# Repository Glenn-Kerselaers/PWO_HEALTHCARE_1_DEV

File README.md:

PWO_HEALTHCARE_1_DEV
====================

Project from PXL for Glenn Kerselaers and Devlin Voets. IMU modules with Bluetooth (BLE) interface for communication with PC.

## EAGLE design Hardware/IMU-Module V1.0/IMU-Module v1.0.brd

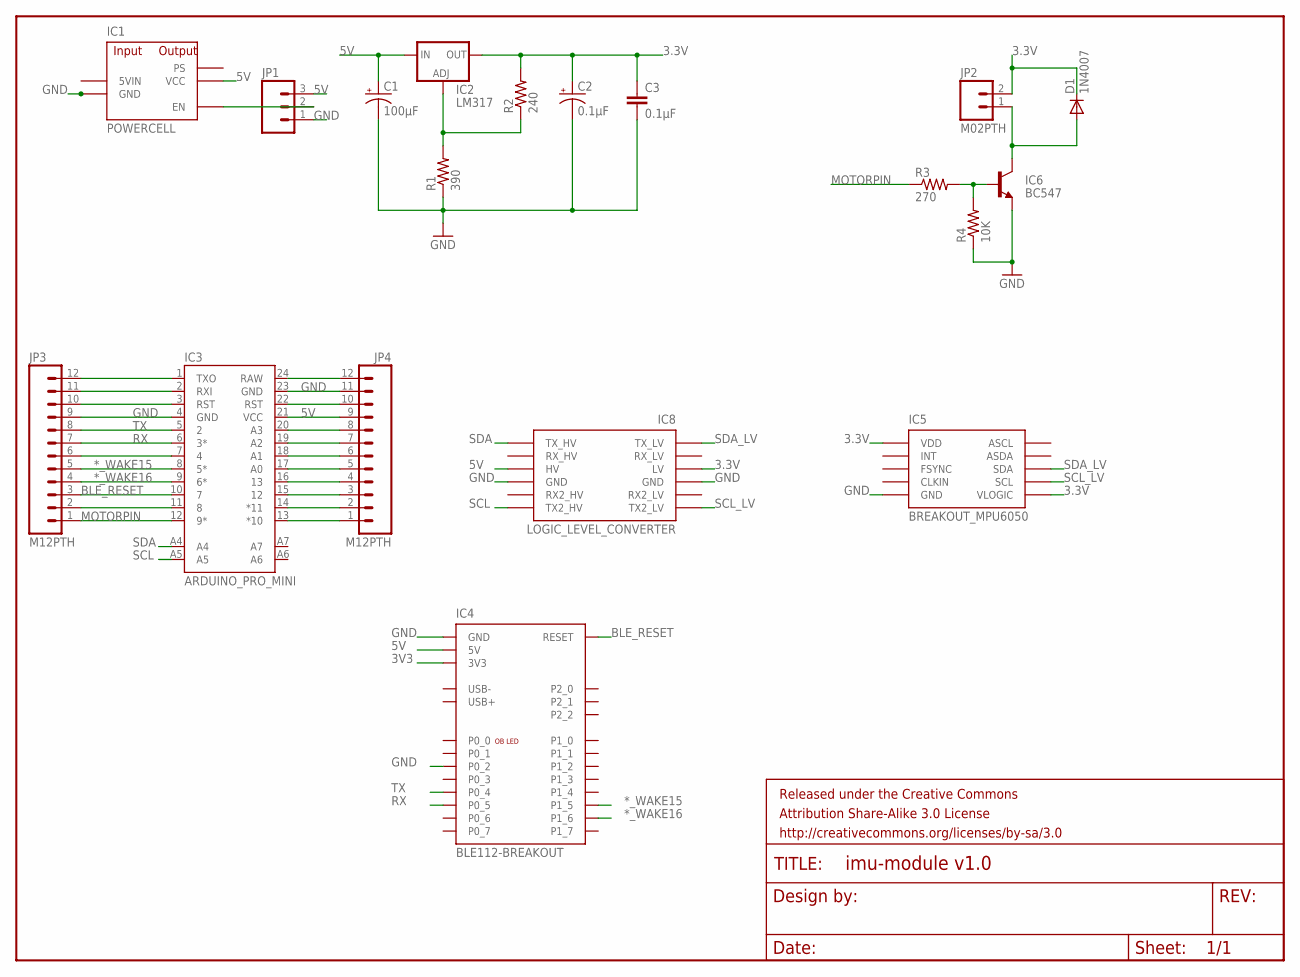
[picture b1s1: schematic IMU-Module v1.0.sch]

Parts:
C1: 100µF; CPOL-RADIAL-100UF-25V
C2: 0.1µF; CPOL-RADIAL-10UF-25V
C3: 0.1µF; 1206
D1: 1N4007; DIODE-1N4001-KIT
FRAME1: FRAME-LETTER; CREATIVE_COMMONS
IC1: POWERCELL
IC2: LM317; SOT223
IC3: ARDUINO_PRO_MINI
IC4: BLE112-BREAKOUT
IC5: BREAKOUT_MPU6050
IC6: BC547; TO-92
IC8: LOGIC_LEVEL_CONVERTER
JP1: M03PTH; 1X03
JP2: M02PTH; 1X02
JP3, JP4: M12PTH; 1X12
R1: 390; 1206
R2: 240; 1206
R3: 270; 1206
R4: 10K; 1206

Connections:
3.3V: C2.1 (+), C3.1, D1.C, IC2.2 (OUT), IC5.VDD, IC5.VLOGIC, IC8.LV, JP2.2, R2.2
3V3: IC4.3V3
5V: C1.1 (+), IC1.VCC, IC2.3 (IN), IC3.21 (VCC), IC4.5V, IC8.HV, JP1.3, JP4.9
5VIN: IC1.5VIN
*_WAKE15: IC3.8 (5*), IC4.P15 (P1_5), JP3.5
*_WAKE16: IC3.9 (6*), IC4.P16 (P1_6), JP3.4
BLE_RESET: IC3.10 (7), IC4.RESET, JP3.3
GND: C1.2 (-), C2.2 (-), C3.2, IC1.GND@1 (GND), IC1.GND@2 (GND), IC3.4 (GND), IC3.23 (GND), IC4.GND, IC4.P02 (P0_2), IC5.GND, IC6.3 (E), IC8.GND@1 (GND), IC8.GND@2 (GND), JP1.1, JP3.9, JP4.11, R1.1, R4.1
MOTORPIN: IC3.12 (9*), JP3.1, R3.1
unnamed: IC6.2 (B), R3.2, R4.2
unnamed: IC1.EN, JP1.2
unnamed: IC2.1 (ADJ), R1.2, R2.1
unnamed: D1.A, IC6.1 (C), JP2.1
unnamed: IC3.7 (4), JP3.6
unnamed: IC3.3 (RST), JP3.10
unnamed: IC3.2 (RXI), JP3.11
unnamed: IC3.1 (TXO), JP3.12
unnamed: IC3.11 (8), JP3.2
unnamed: IC3.20 (A3), JP4.8
unnamed: IC3.19 (A2), JP4.7
unnamed: IC3.18 (A1), JP4.6
unnamed: IC3.17 (A0), JP4.5
unnamed: IC3.16 (13), JP4.4
unnamed: IC3.15 (12), JP4.3
unnamed: IC3.14 (*11), JP4.2
unnamed: IC3.13 (*10), JP4.1
unnamed: IC3.22 (RST), JP4.10
unnamed: IC3.24 (RAW), JP4.12
RX: IC3.6 (3*), IC4.P05 (P0_5), JP3.7
RX2_HV: IC8.HV_RXI_2 (RX2_HV)
RX2_LV: IC8.LV_RXO_2 (RX2_LV)
RX_HV: IC8.HV_RXI_1 (RX_HV)
RX_LV: IC8.LV_RXO_1 (RX_LV)
SCL: IC3.A5, IC8.HV_TXO_2 (TX2_HV)
SCL_LV: IC5.SCL, IC8.LV_TXI_2 (TX2_LV)
SDA: IC3.A4, IC8.HV_TXO_1 (TX_HV)
SDA_LV: IC5.SDA, IC8.LV_TXI_1 (TX_LV)
TX: IC3.5 (2), IC4.P04 (P0_4), JP3.8

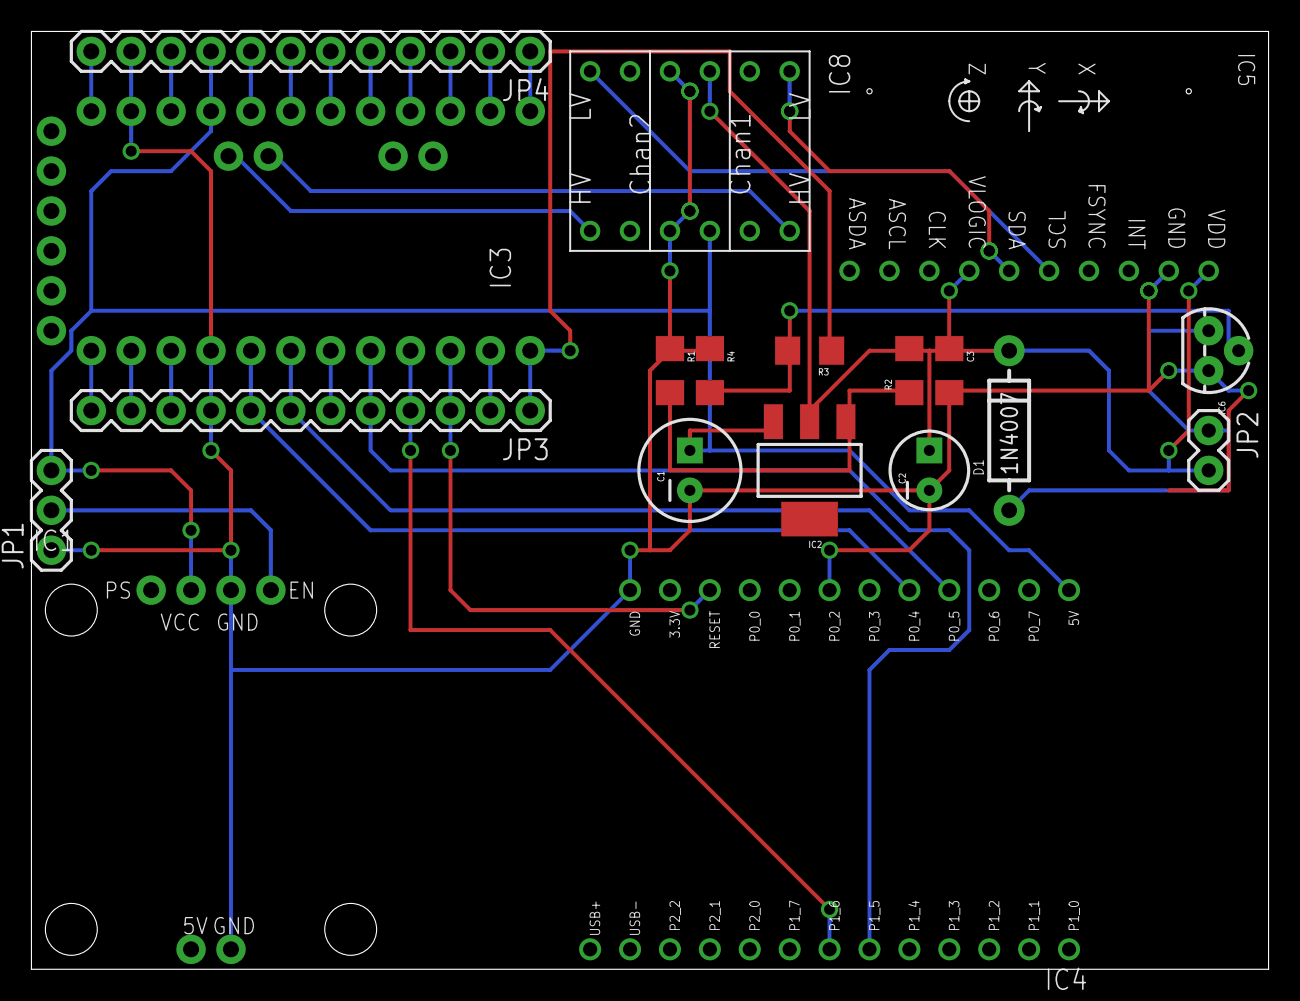
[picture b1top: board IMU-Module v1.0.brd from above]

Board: 2 copper layers, 78.7 x 59.7 mm, 20 parts (0 on the bottom side), 32 nets.

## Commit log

2014-05-26 First update
2014-06-04 Final Update
    Paper, final code.
    The code has still some bugs.
2014-06-04 Processing

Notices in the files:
parts and their libraries:
SparkFun-Aesthetics: Licensing: CC v3.0 Share-Alike You are welcome to use this library for commercial purposes.
SparkFun-Aesthetics: Released under the Creative Commons Attribution Share-Alike 3.0 License
SparkFun-Aesthetics: http://creativecommons.org/licenses/by-sa/3.0
